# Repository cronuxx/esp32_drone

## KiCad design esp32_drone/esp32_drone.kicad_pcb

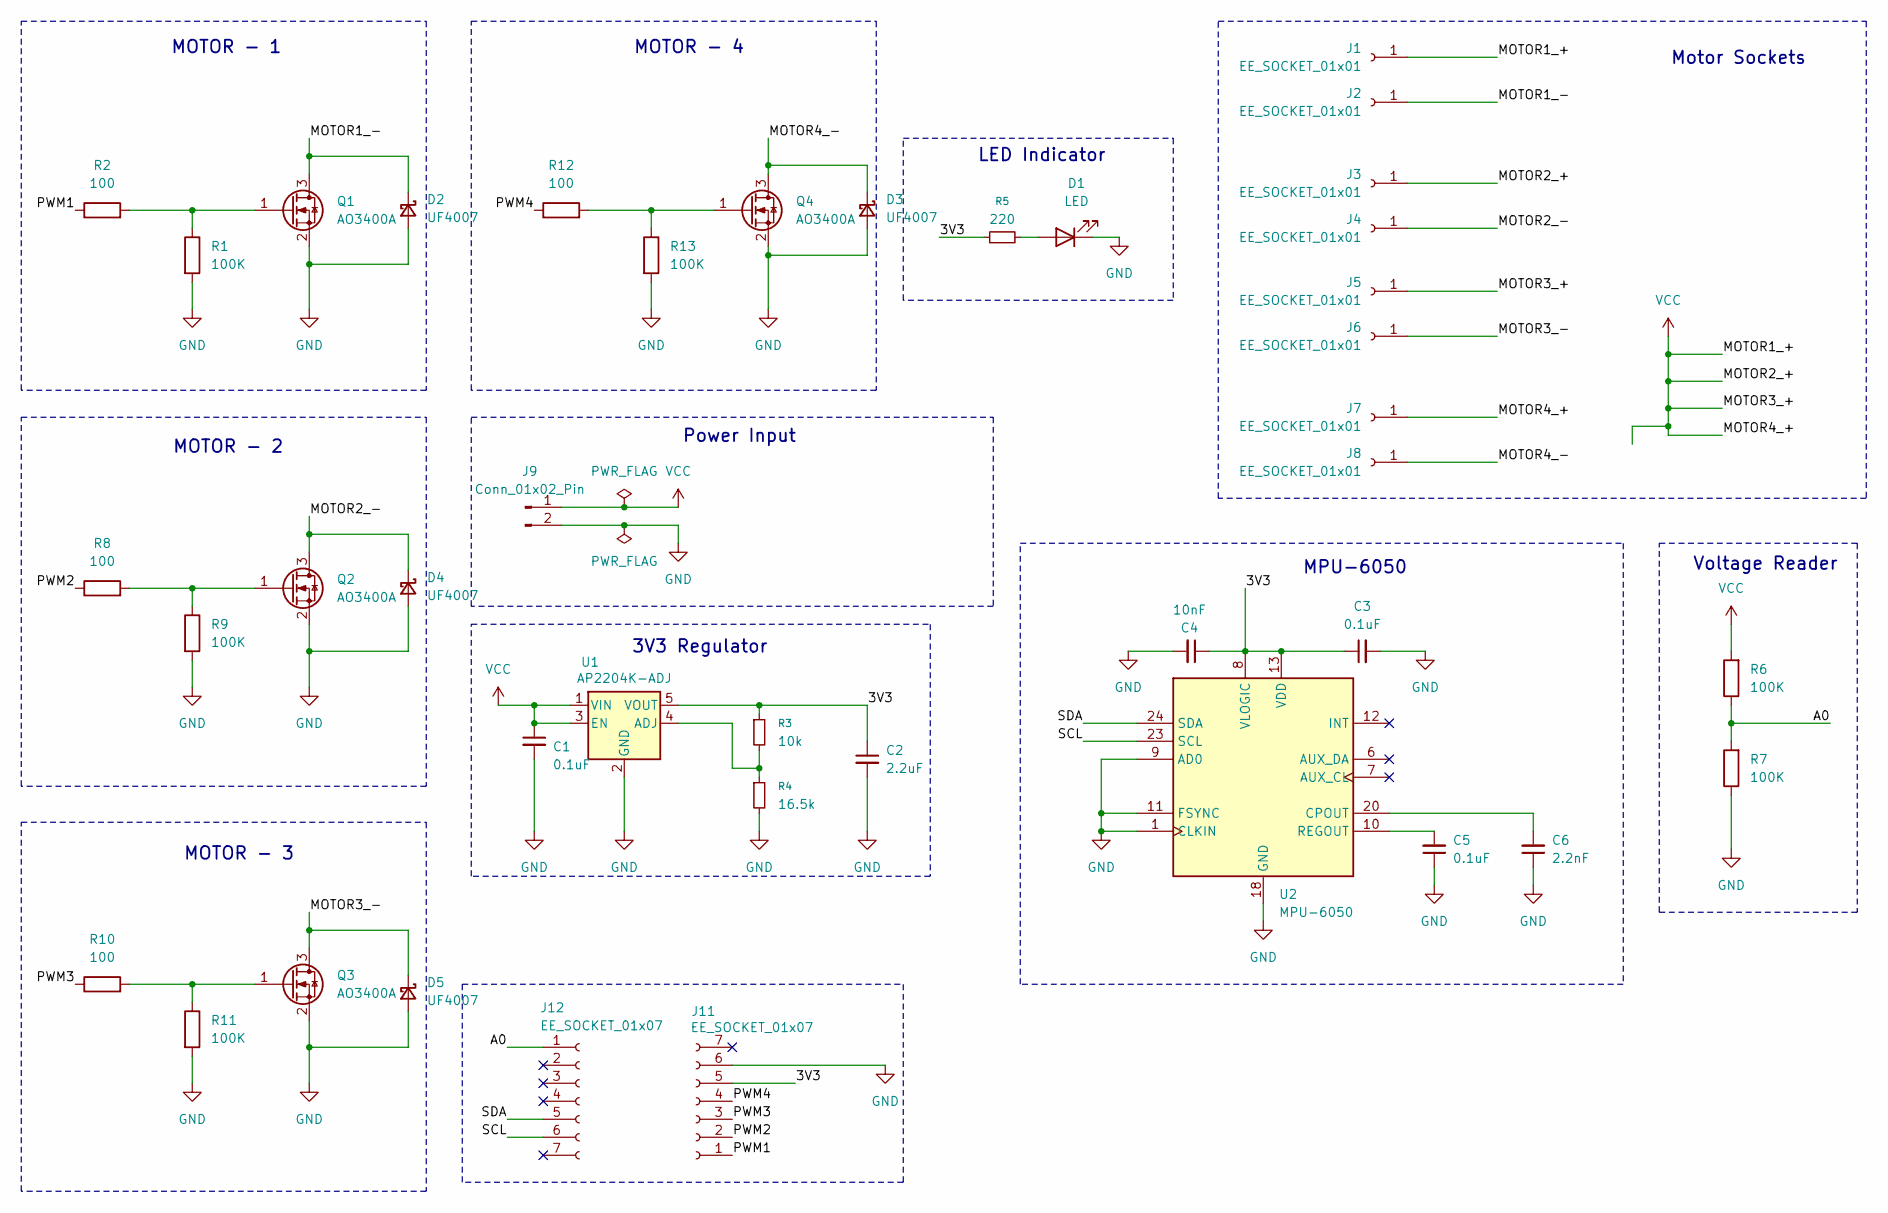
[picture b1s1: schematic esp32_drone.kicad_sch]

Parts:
C1, C3, C5: 0.1uF; C_0805_2012Metric_Pad1.18x1.45mm_HandSolder
C2: 2.2uF; C_0603_1608Metric_Pad1.08x0.95mm_HandSolder
C4: 10nF; C_1206_3216Metric_Pad1.33x1.80mm_HandSolder
C6: 2.2nF; C_0805_2012Metric_Pad1.18x1.45mm_HandSolder
D1: LED; LED_0805_2012Metric_Pad1.15x1.40mm_HandSolder
D2, D3, D4, D5: UF4007; D_SOD-323_HandSoldering
J1, J2, J3, J4, J5, J6, J7, J8: EE_SOCKET_01x01; TestPoint_THTPad_D2.0mm_Drill1.0mm
J9: Conn_01x02_Pin; JST_EH_S2B-EH_1x02_P2.50mm_Horizontal
J11, J12: EE_SOCKET_01x07; PinSocket_1x07_P2.54mm_Vertical
Q1, Q2, Q3, Q4: AO3400A; SOT-23
R1, R6, R7, R9, R11, R13: 100K; R_0603_1608Metric_Pad0.98x0.95mm_HandSolder
R2, R8, R10, R12: 100; R_0603_1608Metric_Pad0.98x0.95mm_HandSolder
R3: 10k; R_0805_2012Metric_Pad1.20x1.40mm_HandSolder
R4: 16.5k; R_1206_3216Metric_Pad1.30x1.75mm_HandSolder
R5: 220; R_0805_2012Metric_Pad1.20x1.40mm_HandSolder
U1: AP2204K-ADJ; SOT-23-5
U2: MPU-6050; QFN-24-1EP_4x4mm_P0.5mm_EP2.7x2.6mm

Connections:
/3V3: C2.1, C3.1, C4.1, J11.5, R3.1, R5.1, U1.5 (VOUT), U2.8 (VLOGIC), U2.13 (VDD)
/A0: J12.1, R6.1, R7.2
/MOTOR1_-: D2.1 (K), J2.1, Q1.3 (D)
/MOTOR2_-: D4.1 (K), J4.1, Q2.3 (D)
/MOTOR3_-: D5.1 (K), J6.1, Q3.3 (D)
/MOTOR4_-: D3.1 (K), J8.1, Q4.3 (D)
/PWM1: J11.1, R2.1
/PWM2: J11.2, R8.1
/PWM3: J11.3, R10.1
/PWM4: J11.4, R12.1
/SCL: J12.6, U2.23 (SCL)
/SDA: J12.5, U2.24 (SDA)
GND: C1.2, C2.2, C3.2, C4.2, C5.1, C6.1, D1.1 (K), D2.2 (A), D3.2 (A), D4.2 (A), D5.2 (A), J9.2, J11.6, Q1.2 (S), Q2.2 (S), Q3.2 (S), Q4.2 (S), R1.2, R4.2, R7.1, R9.2, R11.2, R13.2, U1.2 (GND), U2.1 (CLKIN), U2.9 (AD0), U2.11 (FSYNC), U2.18 (GND)
unnamed: D1.2 (A), R5.2
unnamed: Q1.1 (G), R1.1, R2.2
unnamed: Q2.1 (G), R8.2, R9.1
unnamed: Q3.1 (G), R10.2, R11.1
unnamed: Q4.1 (G), R12.2, R13.1
unnamed: R3.2, R4.1, U1.4 (ADJ)
unnamed: C6.2, U2.20 (CPOUT)
unnamed: C5.2, U2.10 (REGOUT)
VCC: C1.1, J1.1, J3.1, J5.1, J7.1, J9.1, R6.2, U1.1 (VIN), U1.3 (EN)

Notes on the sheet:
MOTOR - 1
Motor Sockets
MOTOR - 4
3V3 Regulator
MPU-6050
Power Input
Voltage Reader
LED Indicator
MOTOR - 3
MOTOR - 2

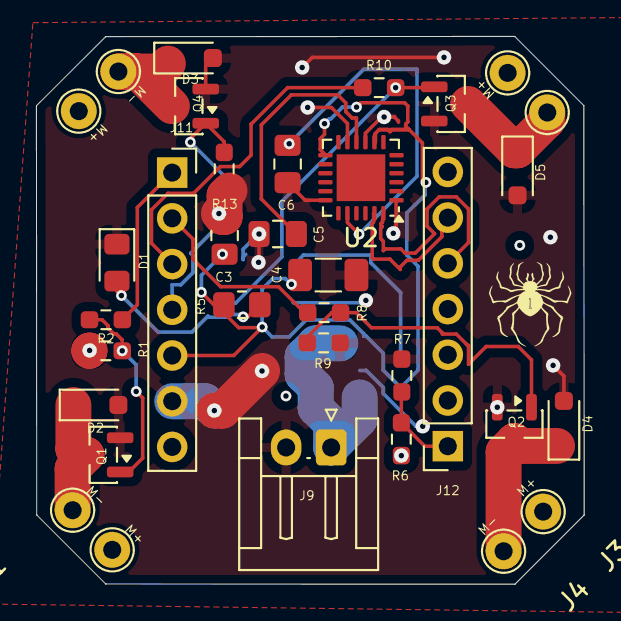
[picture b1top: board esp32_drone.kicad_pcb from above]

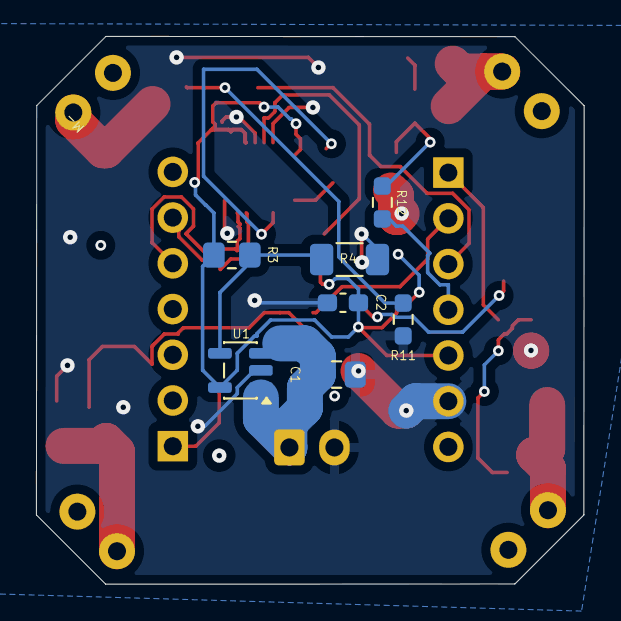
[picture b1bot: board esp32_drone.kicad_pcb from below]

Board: 4 copper layers, 30.4 x 30.4 mm, 41 parts (7 on the bottom side), 22 nets.

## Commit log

2025-10-17 fixed schematic
2025-10-24 finished pcb design
2025-10-24 reduced ground vias
2026-02-05 finished without flyback diode
2026-02-06 finished routing
2026-02-06 finished last product
2026-04-02 updated mpu6050 footprint
